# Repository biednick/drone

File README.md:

# Drones

The drone features 3 oscillators and a tone control, which can be passivly mixed to combine as many oscillators as you want.

## Files
droneSlave_xx .brd and .sch
These are the board and schematic files needed to manufacture PCBs. Gerbers need to be generated in Eagle for manufacturing.

### slaveParts_xx.md
These are the parts lists for each module. A mouser BOM is available in this file as well.

### slavePanel.ai
These are the panels in Adobe Illustrator format. I make my panels on a laser cutter with 1/8 inch acrylic.

## Updates

### 01.1 22AUG18 
Removed the master files because it doesn't work at all.

### 01 25JUN18
First push to GitHub. The slave module has been tested, but the master is untested.

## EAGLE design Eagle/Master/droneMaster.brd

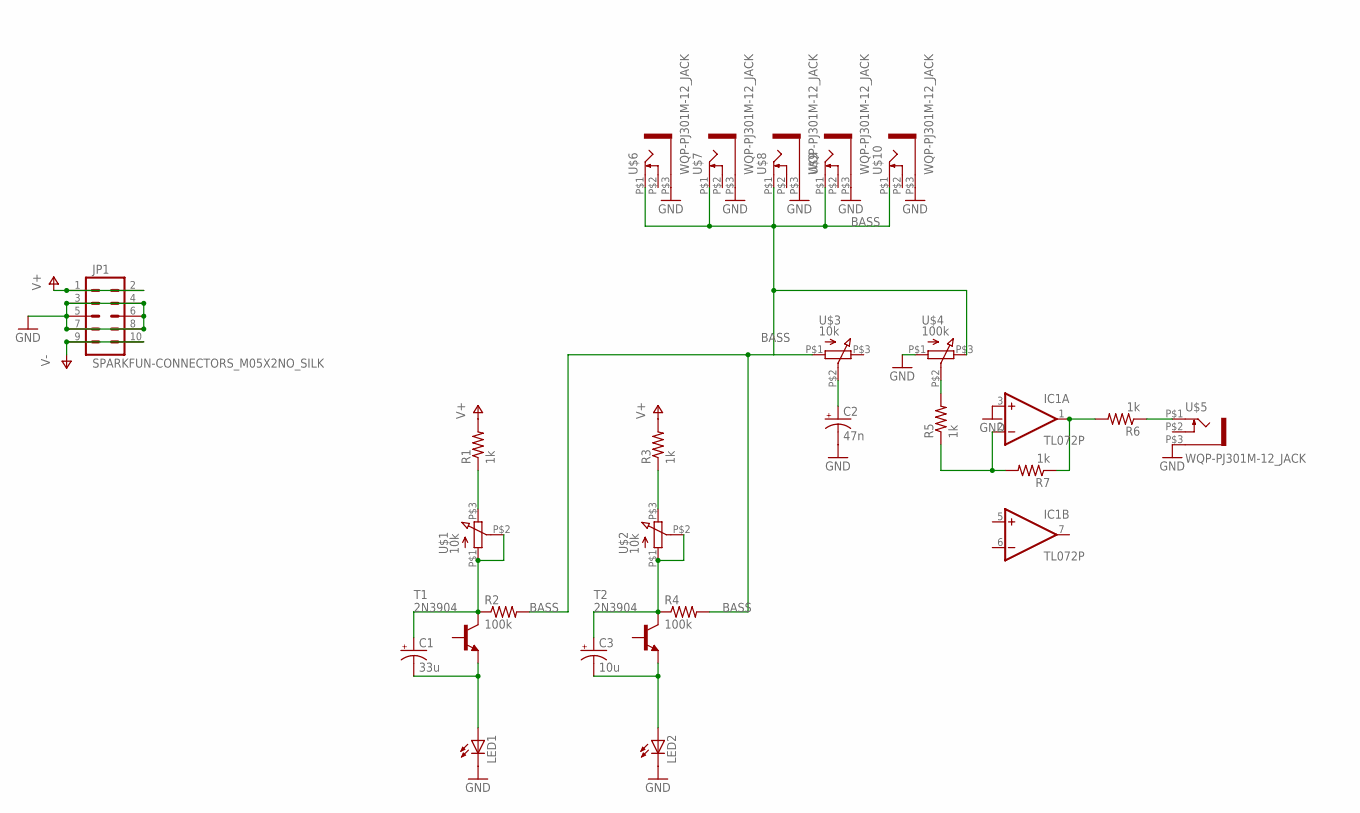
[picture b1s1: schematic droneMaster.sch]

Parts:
C1: 33u; E2,5-7
C2: 47n; E2,5-7
C3: 10u; E2,5-7
IC1: TL072P; DIL08
JP1: SPARKFUN-CONNECTORS_M05X2NO_SILK; SPARKFUN-CONNECTORS_2X5_NOSILK
LED1, LED2: LED5MM
R1, R3, R5, R6, R7: 1k; 0204/7
R2, R4: 100k; 0204/7
T1, T2: 2N3904; TO92
U$1, U$2, U$3: 10k; INSTRUO_Q-POT
U$4: 100k; INSTRUO_Q-POT
U$5, U$6, U$7, U$8, U$9, U$10: WQP-PJ301M-12_JACK

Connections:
BASS: R2.2, R4.2, U$3.P$1 (1), U$4.P$3 (3), U$6.P$1 (2), U$7.P$1 (2), U$8.P$1 (2), U$9.P$1 (2), U$10.P$1 (2)
GND: C2.-, IC1.3 (+IN), JP1.3, JP1.4, JP1.5, JP1.6, JP1.7, JP1.8, LED1.K (C), LED2.K (C), U$4.P$1 (1), U$5.P$3 (1), U$6.P$3 (1), U$7.P$3 (1), U$8.P$3 (1), U$9.P$3 (1), U$10.P$3 (1)
unnamed: R1.1, U$1.P$3 (3)
unnamed: C1.+, R2.1, T1.1 (C), U$1.P$1 (1), U$1.P$2 (2)
unnamed: C1.-, LED1.A, T1.3 (E)
unnamed: R3.1, U$2.P$3 (3)
unnamed: C3.+, R4.1, T2.1 (C), U$2.P$1 (1), U$2.P$2 (2)
unnamed: C3.-, LED2.A, T2.3 (E)
unnamed: C2.+, U$3.P$2 (2)
unnamed: R5.2, U$4.P$2 (2)
unnamed: IC1.1 (OUT), R6.2, R7.1
unnamed: IC1.2 (-IN), R5.1, R7.2
unnamed: R6.1, U$5.P$1 (2)
V+: IC1.8 (V+), JP1.1, JP1.2, R1.2, R3.2
V-: IC1.4 (V-), JP1.9, JP1.10

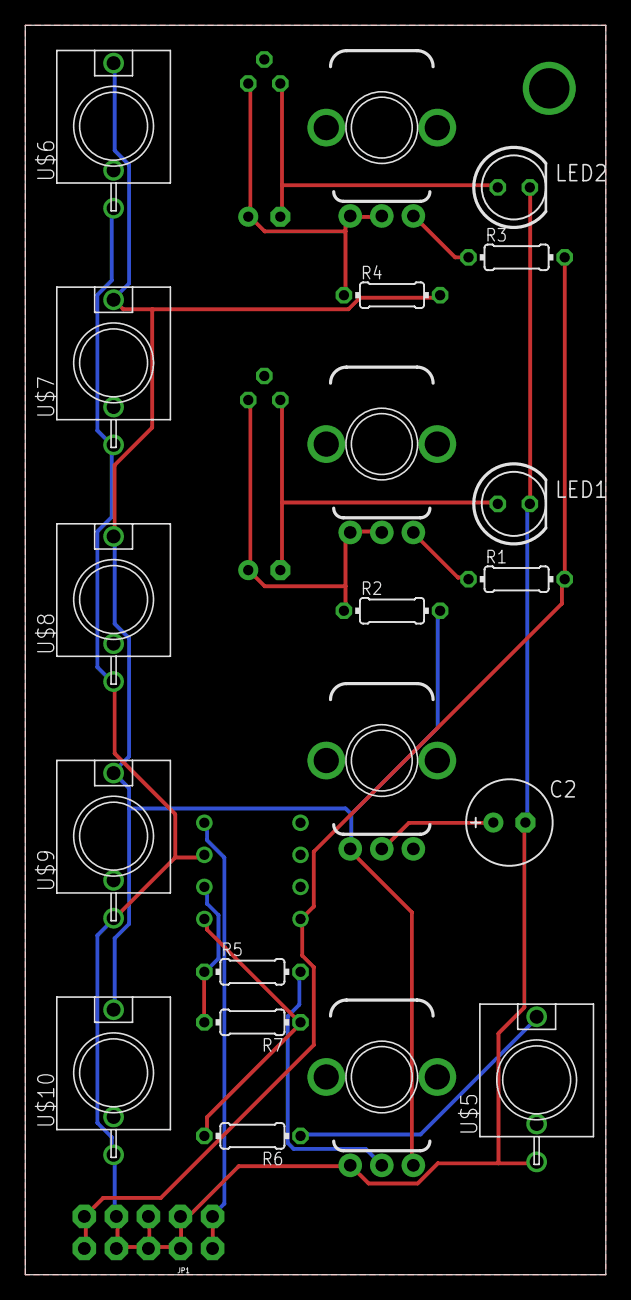
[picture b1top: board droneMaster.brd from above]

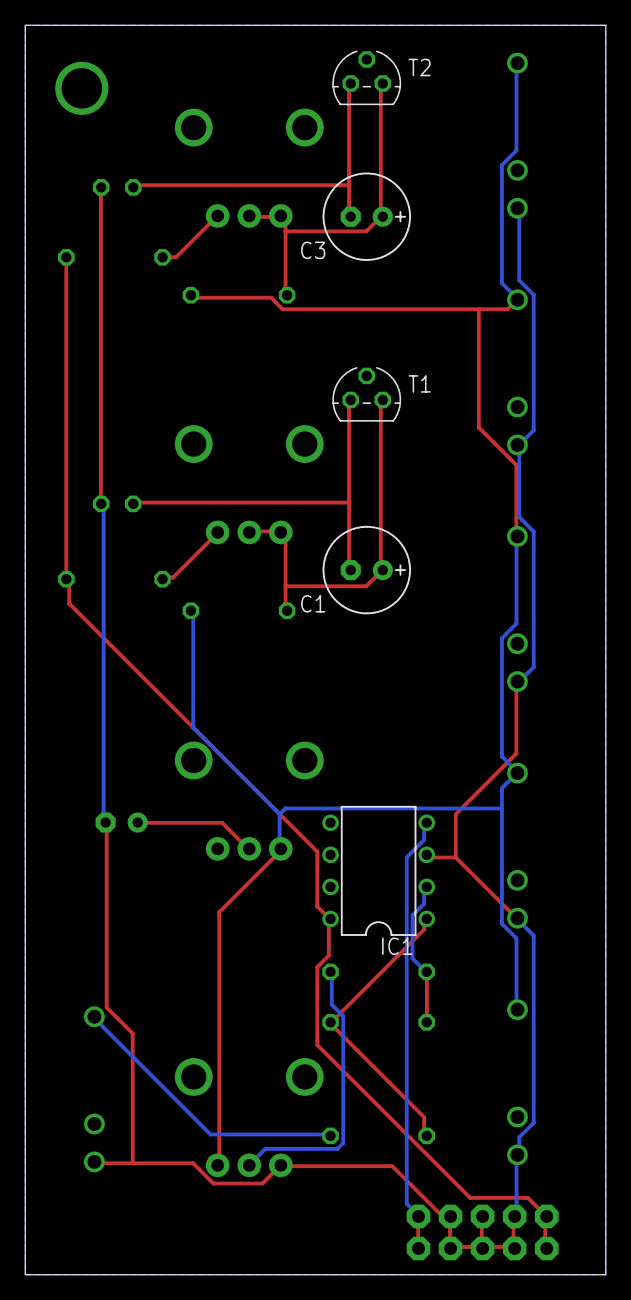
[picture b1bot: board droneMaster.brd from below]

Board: 2 copper layers, 46.0 x 99.0 mm, 26 parts (5 on the bottom side), 15 nets.

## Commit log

2018-07-26 Add site
2018-07-26 Set theme jekyll-theme-minimal
2018-07-31 Update Site
2018-07-31 Add License
2018-07-31 Update parts list
2018-08-22 Add panel, remove master
2018-12-03 Site Update
2018-12-25 ReadMe Fix
2018-12-25 Pages Update
